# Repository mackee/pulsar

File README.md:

# Pulsar - The functional keyboard for creators

## 部品の不足や不具合, その他のお問い合わせ

Twitterの私のアカウントまでDMをしてください [@mackee\_w](https://github.com/mackee_w)

## ビルドガイド

このビルドガイドはRev.2(11キー)版のビルドガイドです。Rev.1(9キー+OLED付き) のビルドガイドはこちら

https://gist.github.com/mackee/b5231e5609be889129ee4aa5c9ab0aaa

### 同梱しているもの

#### Pulsar本体基板

メイン基板と、LEDがついたボトムプレートが一体になっています。

#### トッププレート

本体基板とは別に添付しています。

#### ネジ袋

ネジが入った袋です。袋の中には以下の物が含まれています。

* M2 スペーサー 高さ7.5mm x 8本
* M2 ネジ x 16本

### 別途使用に必要なもの

#### キースイッチ x 11個

Cherry MX互換のキースイッチに対応しています。

[Kailh BOX](https://yushakobo.jp/shop/kailh-box/), [Kailh Speed](https://yushakobo.jp/shop/kailh-speed/), [Gateronスイッチ](https://yushakobo.jp/shop/a0200ga/)の適合を確認しています

#### キーキャップ x 11個

入手されたキースイッチに適合するキーキャップが必要です

#### ノブ/つまみ

親指ロータリーエンコーダ部分に使用するノブです。

軸φ6.1に対応しているつまみが使用できます。また、直径2.3cm以上のつまみはキーキャップと干渉します。

秋月電子で売られている[K-59](http://akizukidenshi.com/catalog/g/gP-12529/)や、千石電商で扱いがある[BR-20](https://www.sengoku.co.jp/mod/sgk_cart/detail.php?code=6A8D-DNEV)が使用できることを確認しています。

### 別途組み立てに必要な道具

* \+ 精密ドライバー
* ラジオペンチ

### 組み立て方

#### 1. 基板を分割する

Pulsar基板本体をメイン基板とボトムプレートに分割します。

4箇所あるので、できるだけ近い部分を持ちつつ折ってください。写真のようにラジオペンチを使うときれいに折れます。

#### 2. ボトムプレートにスペーサーを立てる

ネジ袋からスペーサーを8個全部と、黒いネジを8個取り出します。

ボトムプレートの何も部品がない面から、ネジを差し込み、反対側からスペーサーを取り付けます。

このとき、はじめは手で軽く締めていって、最後に精密ドライバーでネジを、ラジオペンチでスペーサーを持って固く締めます。

8箇所ある穴すべてにスペーサーを立てます。

#### 3. メイン基板をボトムプレートに重ねる

メイン基板を、スペーサーを立てたボトムプレートの上に重ねます。

メイン基板の取り付け穴はスペーサーの直径よりも大きいので、穴の中にスペーサーを通すようにします。

また、ロータリーエンコーダを右下にしたときに、ボトムプレートには 3本のピンヘッダーが、メイン基板にはピンヘッダを通すための穴があります。

電気的に接触するため、メイン基板側の真ん中の穴が少しずれています。重ねたときに、ボトムプレートのピンがメイン基板の穴に刺さるようにします。

止まるまでグググッと押し込みます。

#### 4. トッププレートを取り付ける

ボトムプレートに、メイン基板を重ねた物の上にさらに、トッププレートを重ねます。

スペーサーの位置とトッププレートの位置を合わせて、トッププレートを残りのネジで固定します。

これで、Pulsarの本体は完成です。

#### 5. キースイッチを取り付ける

トッププレートの穴から、キースイッチを差し込んでいきます。

このとき、メイン基板の黒い丸の部品と、キースイッチのピンの位置を合わせます。

また、キースイッチのピンが曲がっているときは、差し込んだときに折れてしまうことがあるため、ラジオペンチなどでまっすぐにしておきます。

トッププレートと、キースイッチの縁が当たるまで、強く押し込みます。

#### 6. キーキャップを取り付ける

キースイッチにキーキャップを取り付けます。

#### 7. つまみ/ノブを取り付ける

ロータリーエンコーダにつまみ/ノブを取り付けます。

これで完成です！ お疲れさまでした。

## デフォルトキーマップ

レバースイッチ押し込みを続けるとLED/RESETレイヤーに入ります。

## キーマップ変更方法

**NOTICE: 本家qmk_firmwareへPull Request予定です。マージされたあとに手順が変わります**

qmk configuratorは現在ロータリーエンコーダに対応していないため、ソースコードを変更してキーマップを変える手順を記述します。

事前に`qmk_firmware`を扱える環境を構築しておきます。

[はじめに - QMK Firmware](https://docs.qmk.fm/#/ja/newbs_getting_started)

参考: [QMK 環境の構築](https://github.com/qmk/qmk_firmware/blob/master/docs/ja/newbs_getting_started.md)

### 1. `pulsar` ブランチを指定して `github.com/mackee/qmk_firmware`をcloneします。

```console
$ git clone -b pulsar github.com/mackee/qmk_firmware
```

すでに`qmk_firmware`のclone済みブランチがある場合は、

```console
$ git remote add mackee https://github.com/mackee/qmk_firmware
$ git fetch mackee pulsar
$ git checkout pulsar
```

と、リモートリポジトリを追加してcheckoutします。

### 2. ファームウェアを書き込む

動作確認のためにファームウェアを書き込みます。頒布時点で書き込まれているキーマップは`default`です。

`qmk_firmware`のディレクトリにCLIターミナル内で移動し、以下のコマンドを実行します。

```console
$ make pulsar/rev2:default:dfu-util
$ qmk flash -kb pulsar/rev2 -km default
```

`ERROR: Bootloader not found. Trying again in 5s.` と表示されたら、右下レバースイッチを押し込みながら、一番右上のキーを押します。すると、書き込みが開始されます。

`Transitioning to dfuMANIFEST state` と表示されたら成功です。

### 3. キー配置を変更する

`default`キーマップをもとにキー配置を変えてみます。

まず、`keyboard/pulsar/keymaps/rev2/default`ディレクトリをコピーして`keyboard/pulsar/rev2/keymaps/mykeymap`ディレクトリを作ります。

```console
$ cp -R keyboard/pulsar/rev2/keymaps/default keyboard/pulsar/rev2/keymaps/mykeymap
```

その後にお好きなテキストエディタで`keyboard/pulsar/rev2/keymaps/mykeymap/keymap.c`を編集します。

例えば`S`と入力されるように設定しているキーを`D`に変更するには以下のように`keymap.c`を変更します。

```diff
@@ -28,7 +28,7 @@ enum {

 const uint16_t PROGMEM keymaps[][MATRIX_ROWS][MATRIX_COLS] = {
   [_BASE] = LAYOUT( /* Base */
-    KC_LSHIFT, KC_A,    KC_S,     KC_Y,    KC_M,             \
+    KC_LSHIFT, KC_A,    KC_D,     KC_Y,    KC_M,             \
     KC_LCTRL,  KC_Z,    KC_X,     KC_C,    KC_V,             \
                                   KC_LALT,                   \
     JP_LBRC,   XXXXXXX, LT(_LED, KC_ENTER), XXXXXXX, JP_RBRC \
```

キーコードの参考ドキュメント: [キーコードまとめ](https://syon.github.io/refills/rid/1471100/)

キーマップの最下段はレバースイッチのキーマップです。レバースイッチには半押しも検知できる機能があるのですが、使いにくいため`default`キーマップでは使っていません。

`JP`がプレフィックスにあるキーコードは、日本語キーボード向けのキーコードです。Windowsですでに日本語キーボードが別にある環境で利用してください。

保存後にキーボードにキーマップを書き込むには、 2と同様の手順で、以下のコマンドを実行します。

```console
$ qmk flash -kb pulsar/rev2 -km mykeymap
```

### 4. ロータリーエンコーダの挙動を変更する

ロータリーエンコーダは`keymap.c`内の`encoder_update_user`関数で挙動を定義しています。

```c
void encoder_update_user(uint8_t index, bool clockwise) {
  if (index == 0) {
    if (clockwise) {
      if (get_mods() & MOD_LCTL) {
        rgblight_step();
      } else if (get_mods() & MOD_LSFT) {
        tap_code(KC_END);
      } else {
        tap_code(KC_MS_WH_DOWN);
      }
    } else {
      if (get_mods() & MOD_LCTL) {
        rgblight_step_reverse();
      } else if (get_mods() & MOD_LSFT) {
        tap_code(KC_HOME);
      } else {
        tap_code(KC_MS_WH_UP);
      }
    }
  }
}
```

`KC_`から始まるキーコードを変更すれば、そのまま挙動を変えることが出来ます。

`clockwise`が`true`の場合は時計回り、`false`のときは反時計回りの場合です。また、`get_mods() & MOD_***`では装飾キーの同時押しの場合の挙動を記述しています。

### LICENSE

#### ハードウェア

回路図, パーツリスト, 基板配線図などハードウェア部分

<br />この 作品 は <a rel="license" href="http://creativecommons.org/licenses/by-sa/4.0/">クリエイティブ・コモンズ 表示 - 継承 4.0 国際 ライセンス</a>の下に提供されています。

#### ソフトウェア

本製品のファームウェアは[qmk firmwareのライセンス](https://qmk.fm/license/)に従います。

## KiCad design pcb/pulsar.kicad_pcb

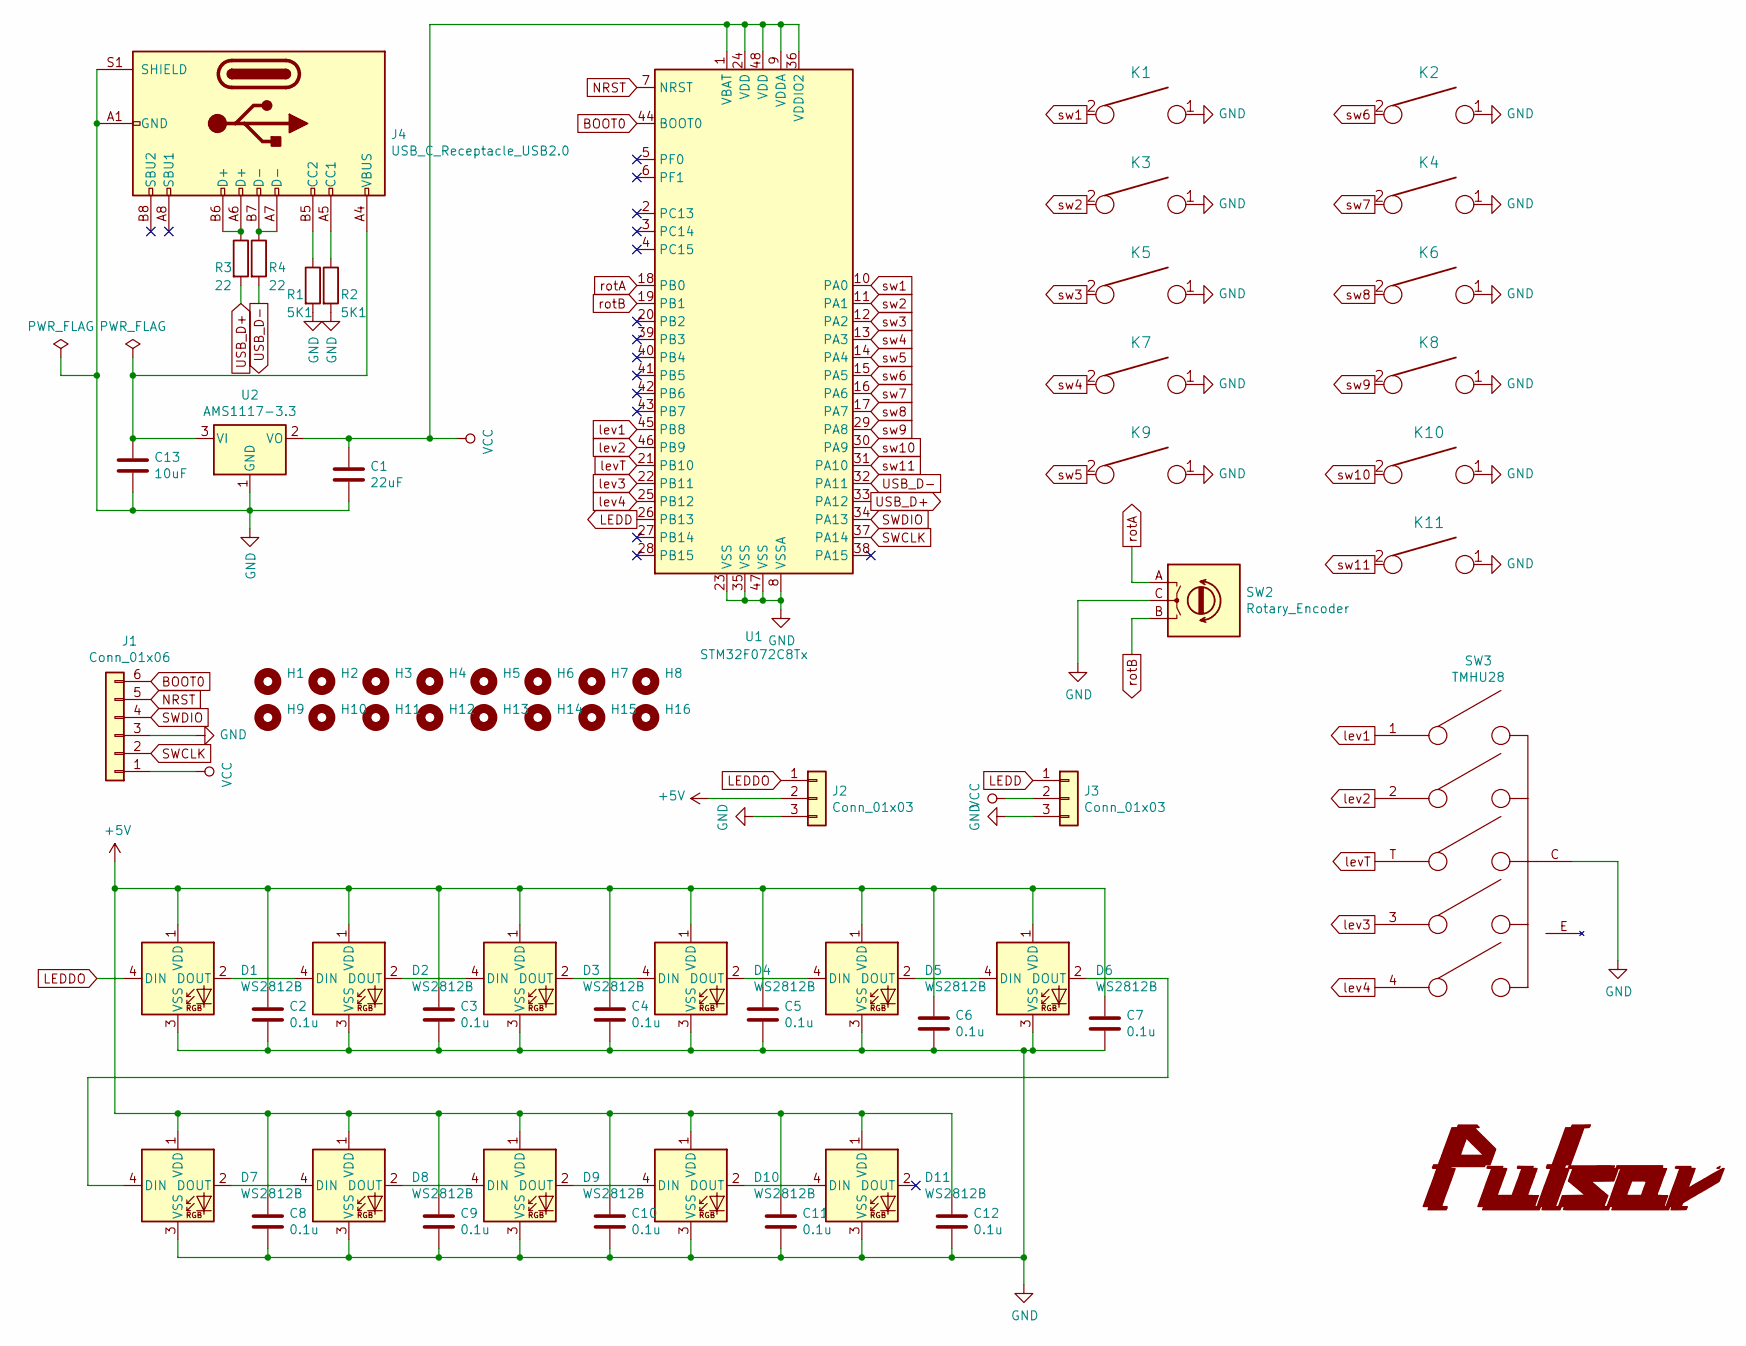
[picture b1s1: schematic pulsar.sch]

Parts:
C1: 22uF; C_0805_HandSoldering
C2, C3, C4, C5, C6, C7, C8, C9, C10, C11, C12: 0.1u; C_0805_HandSoldering
C13: 10uF; C_0805_HandSoldering
D1, D2, D3, D4, D5, D6, D7, D8, D9, D10, D11: WS2812B; LED_SK6812MINI_PLCC4_3.5x3.5mm_P1.75mm
H1, H2, H3, H4, H5, H6, H7, H9: MountingHole; MountingHole_4.3mm_M4
H8, H10, H11, H12, H13, H14, H15, H16: MountingHole; MountingHole_2.2mm_M2
J1: Conn_01x06; Pin_Header_Straight_1x06_Pitch2.54mm
J2: Conn_01x03; Pin_Header_Straight_1x03_Pitch2.54mm_SMD_Pin1Left
J3: Conn_01x03; 3pin-zigzag
J4: USB_C_Receptacle_USB2.0; Mid_Mount-USB_C_HandSoldering
K1, K2, K3, K4, K5, K6, K7, K8, K9, K10, K11: KEYSW; Kailh_socket
R1, R2: 5K1; R_0805_HandSoldering
R3, R4: 22; R_0805_HandSoldering
SW2: Rotary_Encoder; RotaryEncoder_Alps_EC12E_Vertical_H20mm
SW3: TMHU28
U1: STM32F072C8Tx; LQFP-48_7x7mm_Pitch0.5mm
U2: AMS1117-3.3; SOT-223-3_TabPin2

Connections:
+5V: C2.1, C3.1, C4.1, C5.1, C6.1, C7.1, C8.1, C9.1, C10.1, C11.1, C12.1, D1.1 (VDD), D2.1 (VDD), D3.1 (VDD), D4.1 (VDD), D5.1 (VDD), D6.1 (VDD), D7.1 (VDD), D8.1 (VDD), D9.1 (VDD), D10.1 (VDD), D11.1 (VDD), J2.2
BOOT0: J1.6, U1.44 (BOOT0)
GND: C1.2, C2.2, C3.2, C4.2, C5.2, C6.2, C7.2, C8.2, C9.2, C10.2, C11.2, C12.2, C13.2, D1.3 (VSS), D2.3 (VSS), D3.3 (VSS), D4.3 (VSS), D5.3 (VSS), D6.3 (VSS), D7.3 (VSS), D8.3 (VSS), D9.3 (VSS), D10.3 (VSS), D11.3 (VSS), J1.3, J2.3, J3.3, J4.A1 (GND), J4.A12 (GND), J4.B1 (GND), J4.B12 (GND), J4.S1 (SHIELD), K1.1, K2.1, K3.1, K4.1, K5.1, K6.1, K7.1, K8.1, K9.1, K10.1, K11.1, R1.2, R2.2, SW2.C, SW3.C, U1.8 (VSSA), U1.23 (VSS), U1.35 (VSS), U1.47 (VSS), U2.1 (GND)
LEDD: J3.1, U1.26 (PB13)
LEDDO: D1.4 (DIN), J2.1
NRST: J1.5, U1.7 (NRST)
unnamed: C13.1, J4.A4 (VBUS), J4.A9 (VBUS), J4.B4 (VBUS), J4.B9 (VBUS), U2.3 (VI)
unnamed: D1.2 (DOUT), D2.4 (DIN)
unnamed: D2.2 (DOUT), D3.4 (DIN)
unnamed: D3.2 (DOUT), D4.4 (DIN)
unnamed: D4.2 (DOUT), D5.4 (DIN)
unnamed: D5.2 (DOUT), D6.4 (DIN)
unnamed: D6.2 (DOUT), D7.4 (DIN)
unnamed: D7.2 (DOUT), D8.4 (DIN)
unnamed: D8.2 (DOUT), D9.4 (DIN)
unnamed: D10.2 (DOUT), D11.4 (DIN)
unnamed: D9.2 (DOUT), D10.4 (DIN)
unnamed: J4.A5 (CC1), R2.1
unnamed: J4.A6 (D+), J4.B6 (D+), R3.1
unnamed: J4.A7 (D-), J4.B7 (D-), R4.1
unnamed: J4.B5 (CC2), R1.1
SWCLK: J1.2, U1.37 (PA14)
SWDIO: J1.4, U1.34 (PA13)
USB_D+: R3.2, U1.33 (PA12)
USB_D-: R4.2, U1.32 (PA11)
VCC: C1.1, J1.1, J3.2, U1.1 (VBAT), U1.9 (VDDA), U1.24 (VDD), U1.36 (VDDIO2), U1.48 (VDD), U2.2 (VO)
lev1: SW3.1, U1.45 (PB8)
lev2: SW3.2, U1.46 (PB9)
lev3: SW3.3, U1.22 (PB11)
lev4: SW3.4, U1.25 (PB12)
levT: SW3.T, U1.21 (PB10)
rotA: SW2.A, U1.18 (PB0)
rotB: SW2.B, U1.19 (PB1)
sw1: K1.2, U1.10 (PA0)
sw2: K3.2, U1.11 (PA1)
sw3: K5.2, U1.12 (PA2)
sw4: K7.2, U1.13 (PA3)
sw5: K9.2, U1.14 (PA4)
sw6: K2.2, U1.15 (PA5)
sw7: K4.2, U1.16 (PA6)
sw8: K6.2, U1.17 (PA7)
sw9: K8.2, U1.29 (PA8)
sw10: K10.2, U1.30 (PA9)
sw11: K11.2, U1.31 (PA10)

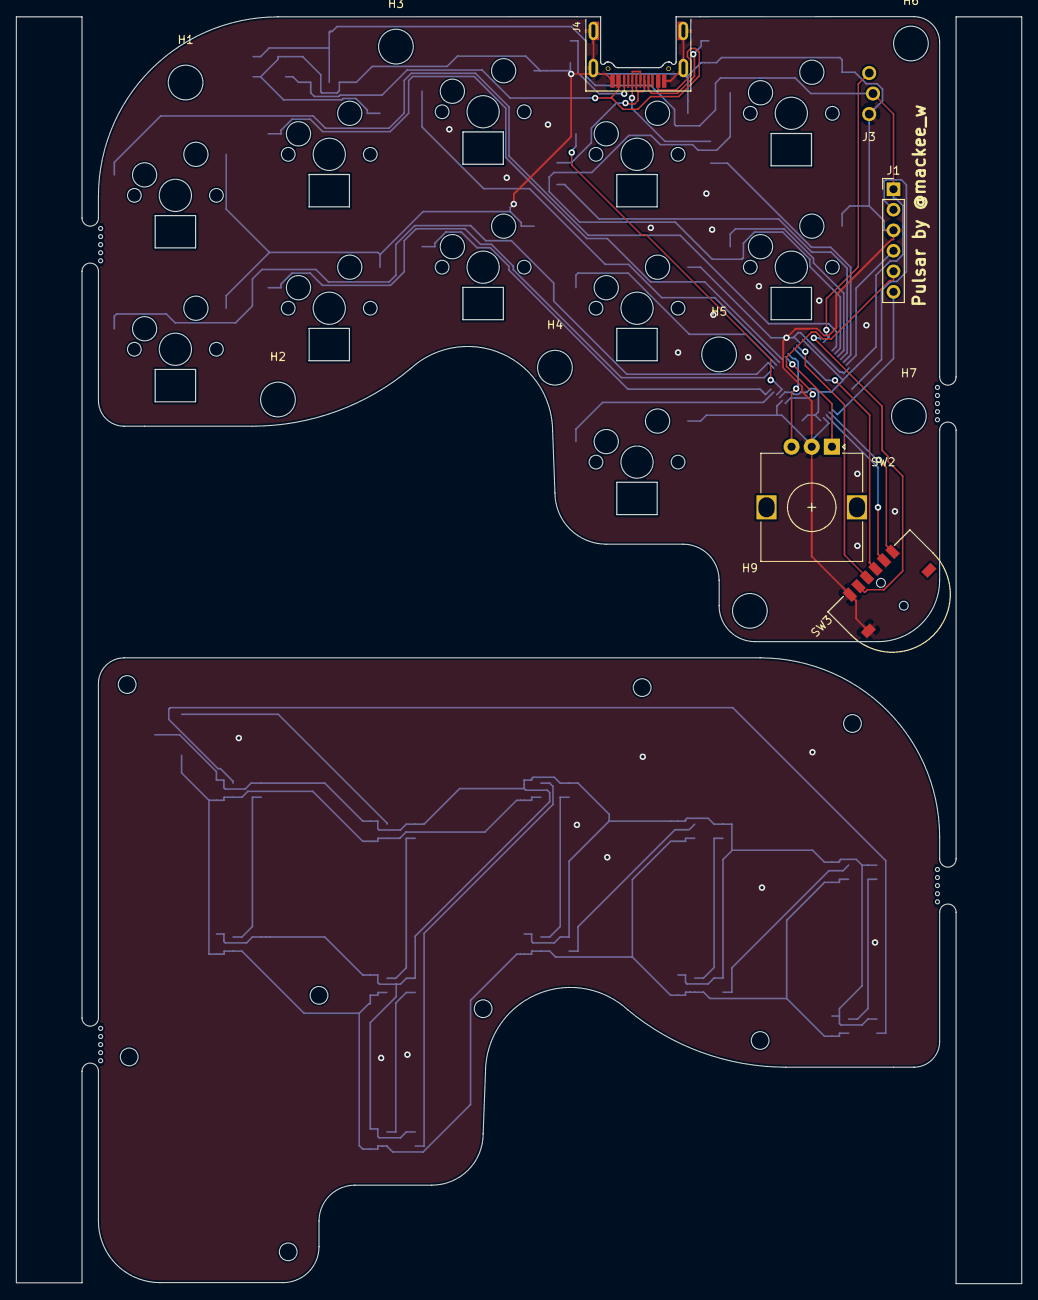
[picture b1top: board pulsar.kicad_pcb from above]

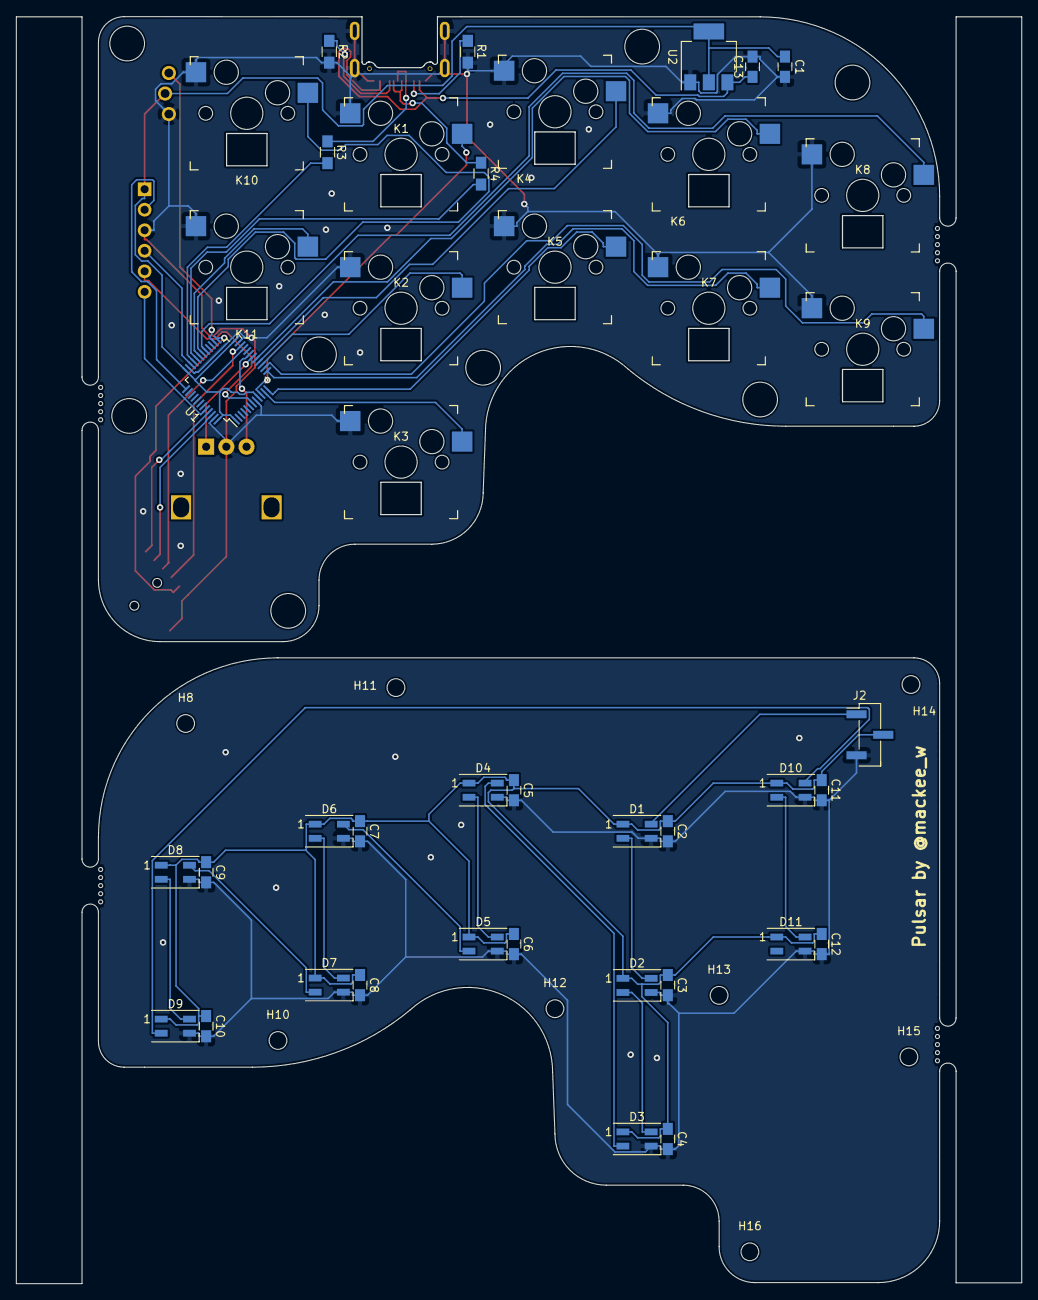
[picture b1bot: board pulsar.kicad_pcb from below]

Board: 2 copper layers, 124.4 x 156.8 mm, 63 parts (39 on the bottom side), 44 nets.

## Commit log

2019-11-03 pulsar rev1
2020-02-23 update pcb: rev2.0 - 11 keys
2020-03-15 add plate pcb
2020-03-15 add README.md
2020-03-20 update document
2021-02-20 qmkの導入に関して公式の和訳ドキュメントとqmkコマンドを使うようにした

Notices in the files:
README.md:
CC BY-SA 4.0
